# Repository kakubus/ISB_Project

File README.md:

<hr/>
<h5>Politechnika Śląska</br>
Wydział Automatyki Elektroniki i Informatyki</br>
Automatyka i Robotyka Sem V (2020/2021). Grupa TI-4 (s. 5)</h5>
<hr/>
<h2>Inteligentny sterownik bramy - <i>Projekt na Systemy Mikroprocesorowe</i></h2>
<b>Autorzy:</b><br/>
<ul>
   <li><i>Jakub Kaniowski (https://github.com/kakubus)</i></li>
   <li><i>Szymon Ciemała (https://github.com/szymciem8)</i></li>
</ul>
<hr/>

<h4>Struktura repozytorium:</h4>

1. <b>main</b> - Główny program sterownika</i>
    * W tym miejscu znajdują się główne pliki dot. kodów źródłowych projektu - kod do ESP (*.ino).
2. <b>multiplexerTools</b> - Program obsługi multipleksera</i>
    * W tym miejscu znajdują się przydatne pliki do obsługi multipleksera. Może się przydać na przyszłość (*.ino).
3. <b>motorTools</b> - Prosty program sterowania L293D</i>
    * W tym miejscu znajdują się przydatne pliki do obsługi L293D. Może się przydać na przyszłość (*.ino).
4. <b>Documentation</b> - <i>folder plików</i>
    * W tym miejscu, znajduje się cała dokumentacja projektu. 
        * <b>Raport końcowy wymagany do prezentacji projektu na zajęciach.</b>
        * Dokumentacja związana z elementami stosowanymi w projekcie.
        * Inne pliki tymczasowe, schematy elektryczne, projekty płytek PCB.
6. <b>RFID</b> - <i>Program testowy dla modułu RFID</i>
 </br></br>   
 <hr/>
<p align="center">
   <p>Zaprojektowana i wytrawiona płytka PCB:<br/></p>
   
   <p>Skonstruowany sterownik:<br/></p>
   
   <p>Platforma testowa:<br/></p>
   
</p>
  <br/>
  <hr/>  
  <h6>Start projektu: Październik 2020 | Zakończenie: Grudzień 2020</h6>
  <hr/>

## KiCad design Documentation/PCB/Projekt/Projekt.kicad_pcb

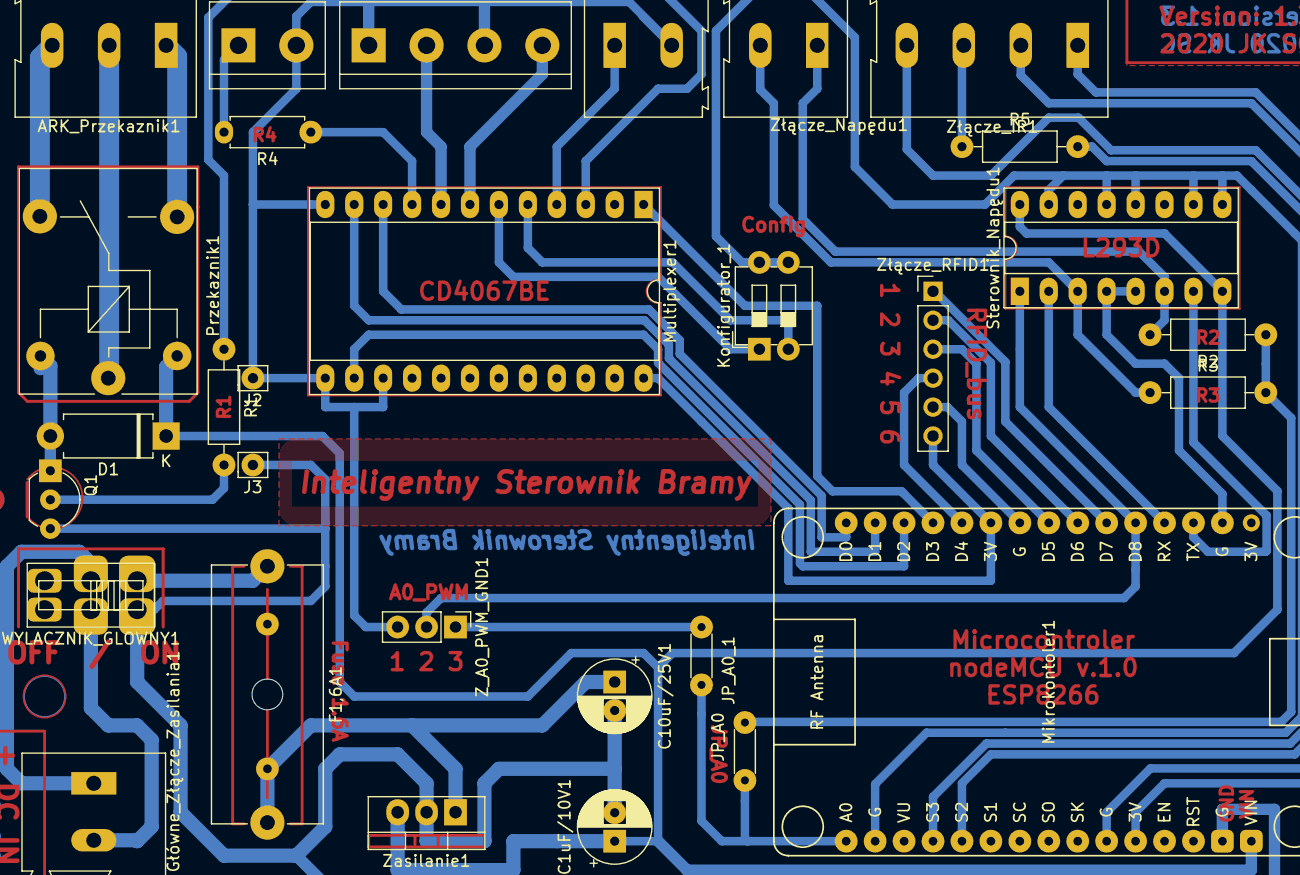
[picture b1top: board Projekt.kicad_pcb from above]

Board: 2 copper layers, 30 parts (0 on the bottom side), 39 nets.

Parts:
ARK_Krancowki1: Conn_01x04_Female; TerminalBlock_bornier-4_P5.08mm
ARK_Powiad_LED1: Conn_01x02_Female; TerminalBlock_bornier-2_P5.08mm
ARK_Przekaznik1: Conn_01x03_Male; TerminalBlock_Altech_AK300-3_P5.00mm
C1uF/10V1, C10uF/25V1: CP1; CP_Radial_D6.3mm_P2.50mm
D1: D; D_DO-15_P10.16mm_Horizontal
F1,6A1: Fuse; MocownaieFuseholder_Cylinder-5x20mm_Schurter_0031_8201_Hori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
Główne_Złącze_Zasilania1: Conn_01x02_Female; TerminalBlock_Altech_AK300-2_P5.00mm
J2: Conn_01x01_Female; Pin_D0.9mm_L10.0mm_W2.4mm_FlatFork
J3: Conn_01x01_Male; Pin_D0.9mm_L10.0mm_W2.4mm_FlatFork
JP_A0, JP_A0_1: Jumper; R_Axial_DIN0204_L3.6mm_D1.6mm_P5.08mm_Horizontal
Konfigurator_1: SW_DIP_x02; SW_DIP_SPSTx02_Slide_6.7x6.64mm_W7.62mm_P2.54mm_LowProfile
Mikrokontoler1: NodeMCU1.0(ESP-12E); NodeMCU1.0(12-E)
Multiplexer1: CD4067BE; DIP-24_W15.24mm_Socket_LongPads
Przekaznik1: SANYOU_SRD_Form_C; Relay_SPDT_SANYOU_SRD_Series_Form_C
Q1: BC547; TO-92_Inline_Wide
R1: R5k; R_Axial_DIN0207_L6.3mm_D2.5mm_P10.16mm_Horizontal
R2: R220; R_Axial_DIN0207_L6.3mm_D2.5mm_P10.16mm_Horizontal
R3: R330; R_Axial_DIN0207_L6.3mm_D2.5mm_P10.16mm_Horizontal
R4: R330; R_Axial_DIN0207_L6.3mm_D2.5mm_P7.62mm_Horizontal
R5: R100; R_Axial_DIN0207_L6.3mm_D2.5mm_P10.16mm_Horizontal
Sterownik_Napędu1: L293D; DIP-16_W7.62mm_Socket_LongPads
WYLACZNIK_GLOWNY1: SW_DPST; SW_E_DPDT
Włącznik_Sterowania_Ręcznego1: SW_Push; TerminalBlock_Altech_AK300-2_P5.00mm
Z_A0_PWM_GND1: Zlacze_dev; PinHeader_1x03_P2.54mm_Vertical
Zasilanie1: LM7805_TO220; TO-220-3_Vertical
Złącze_IR1: 01; TerminalBlock_Altech_AK300-4_P5.00mm
Złącze_Napędu1: Conn_01x02_Female; TerminalBlock_Altech_AK300-2_P5.00mm
Złącze_RFID1: Conn_01x06_Female; PinHeader_1x06_P2.54mm_Vertical

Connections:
+12V: Główne_Złącze_Zasilania1.1, WYLACZNIK_GLOWNY1.3
/+3V: Mikrokontoler1.16, Mikrokontoler1.25, Multiplexer1.24, Złącze_RFID1.6
/+5V: C1uF/10V1.1, D1.1, Mikrokontoler1.15, Przekaznik1.2, Sterownik_Napędu1.8, Sterownik_Napędu1.16, Zasilanie1.3
/A0: JP_A0.1, JP_A0.2, JP_A0_1.2, Mikrokontoler1.1, R2.1, R3.2
/IR_emitter: Mikrokontoler1.4, R5.2
/IR_receiver: Mikrokontoler1.5, Złącze_IR1.4
/MUX_3Pin: Multiplexer1.3, R1.1
/PWM_mDC: Mikrokontoler1.20, Sterownik_Napędu1.1, Z_A0_PWM_GND1.2
GND: ARK_Krancowki1.1, ARK_Krancowki1.3, ARK_Powiad_LED1.2, C1uF/10V1.2, C10uF/25V1.2, Główne_Złącze_Zasilania1.2, J2.1, J3.1, Konfigurator_1.3, Konfigurator_1.4, Mikrokontoler1.14, Mikrokontoler1.17, Mikrokontoler1.24, Multiplexer1.12, Multiplexer1.13, Multiplexer1.15, Q1.3, Sterownik_Napędu1.4, Sterownik_Napędu1.5, Sterownik_Napędu1.9, Sterownik_Napędu1.10, Sterownik_Napędu1.12, Sterownik_Napędu1.13, Sterownik_Napędu1.15, WYLACZNIK_GLOWNY1.1, WYLACZNIK_GLOWNY1.2, Włącznik_Sterowania_Ręcznego1.2, Z_A0_PWM_GND1.3, Zasilanie1.2, Złącze_RFID1.5
unnamed: ARK_Krancowki1.2, Multiplexer1.8
unnamed: ARK_Krancowki1.4, Multiplexer1.7
unnamed: ARK_Powiad_LED1.1, R4.2
unnamed: ARK_Przekaznik1.1, Przekaznik1.3
unnamed: ARK_Przekaznik1.2, Przekaznik1.1
unnamed: ARK_Przekaznik1.3, Przekaznik1.4
unnamed: C10uF/25V1.1, F1,6A1.2, Zasilanie1.1
unnamed: D1.2, Przekaznik1.5, Q1.1
unnamed: F1,6A1.1, WYLACZNIK_GLOWNY1.4
unnamed: JP_A0_1.1, Z_A0_PWM_GND1.1
unnamed: Konfigurator_1.1, Multiplexer1.6
unnamed: Konfigurator_1.2, Multiplexer1.5
unnamed: Mikrokontoler1.10, Złącze_IR1.2
unnamed: Mikrokontoler1.11, Złącze_IR1.1
unnamed: Mikrokontoler1.18, Sterownik_Napędu1.7
unnamed: Mikrokontoler1.19, Sterownik_Napędu1.2
unnamed: Mikrokontoler1.21, Złącze_RFID1.1
unnamed: Mikrokontoler1.22, Złącze_RFID1.2
unnamed: Mikrokontoler1.23, Złącze_RFID1.3
unnamed: Mikrokontoler1.26, Złącze_RFID1.4
unnamed: Mikrokontoler1.27, Multiplexer1.1
unnamed: Mikrokontoler1.28, Multiplexer1.14
unnamed: Mikrokontoler1.29, Multiplexer1.11
unnamed: Mikrokontoler1.30, Multiplexer1.10
unnamed: Multiplexer1.4, Włącznik_Sterowania_Ręcznego1.1
unnamed: Multiplexer1.9, R4.1
unnamed: Q1.2, R1.2
unnamed: R2.2, Sterownik_Napędu1.6, Złącze_Napędu1.1
unnamed: R3.1, Sterownik_Napędu1.3, Złącze_Napędu1.2
unnamed: R5.1, Złącze_IR1.3

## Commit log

2022-06-17 View
